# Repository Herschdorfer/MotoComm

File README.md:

# MotoComm
This is the Main Repo for the MotoComm Project

# Thx to Tomas Kovacik for uploading a library to github : https://github.com/tomaskovacik/kicad-library

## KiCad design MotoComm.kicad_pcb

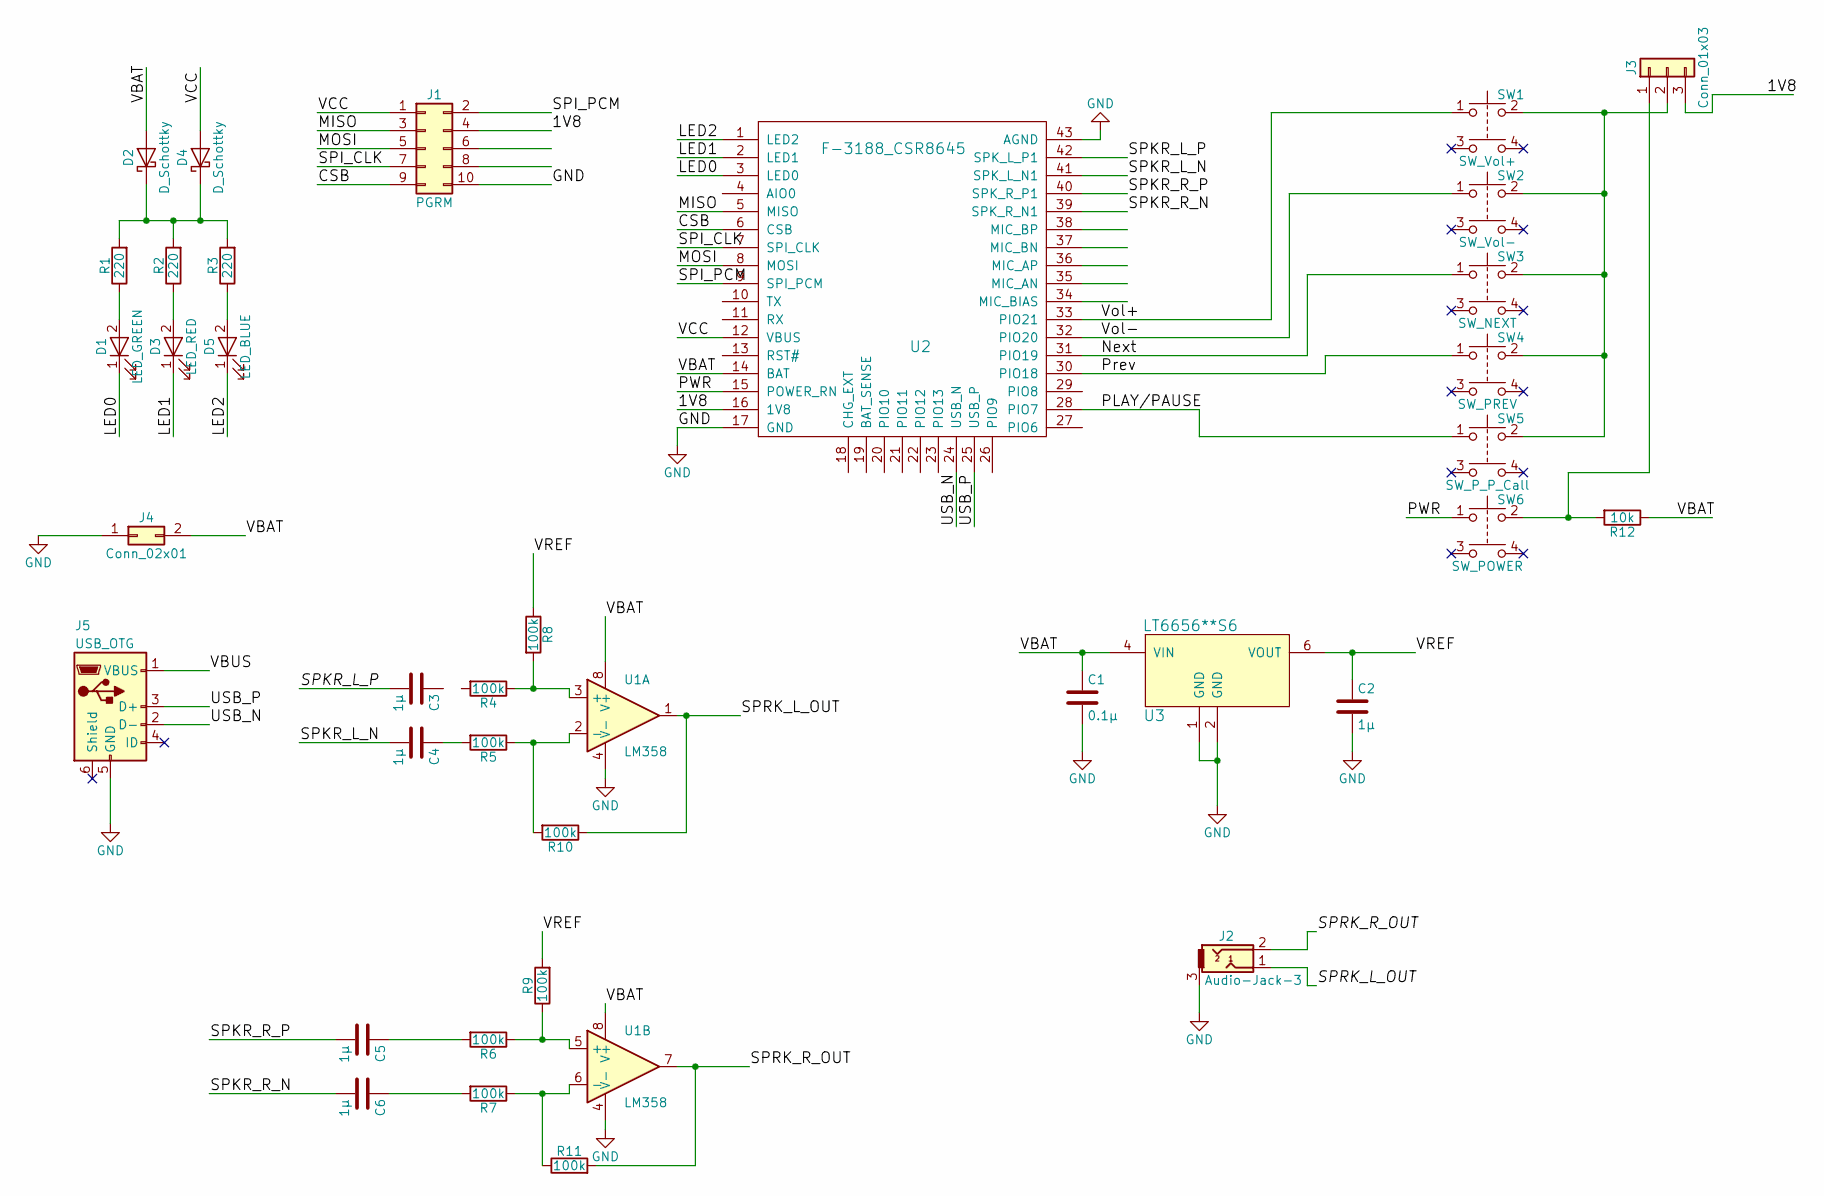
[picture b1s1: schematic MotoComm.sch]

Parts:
C1: 0.1µ; C_0805_HandSoldering
C2, C3, C4, C5, C6: 1µ; C_0805_HandSoldering
D1: LED_GREEN; LED_1206_HandSoldering
D2, D4: D_Schottky; D_1206
D3: LED_RED; LED_1206_HandSoldering
D5: LED_BLUE; LED_1206_HandSoldering
J1: PGRM; Pin_Header_Straight_2x05_Pitch2.54mm
J2: Audio-Jack-3; Stereo_Jack_3.5mm_Switch_Ledino_KB3SPRS
J3: Conn_01x03; Pin_Header_Straight_1x03_Pitch2.54mm
J4: Conn_02x01; JST_ACH_BM02B-ACHSS_02x1.20mm_Angled
J5: USB_OTG; USB_Micro-B
R1, R2, R3: 220; R_0805_HandSoldering
R4, R5, R6, R7, R8, R9, R10, R11: 100k; R_0805_HandSoldering
R12: 10k; R_0805_HandSoldering
SW1: SW_Vol+; SW_TH_Tactile_Omron_B3F-10xx
SW2: SW_Vol-; SW_TH_Tactile_Omron_B3F-10xx
SW3: SW_NEXT; SW_TH_Tactile_Omron_B3F-10xx
SW4: SW_PREV; SW_TH_Tactile_Omron_B3F-10xx
SW5: SW_P_P_Call; SW_TH_Tactile_Omron_B3F-10xx
SW6: SW_POWER; SW_TH_Tactile_Omron_B3F-10xx
U1: LM358; TSSOP-8_3x3mm_Pitch0.65mm
U2: F-3188_CSR8645; F-3188_CSR8645_no_silk_under_antena
U3: LT6656**S6; TSOT-23-8_HandSoldering

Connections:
/1V8: J1.4, J3.3, U2.16 (1V8)
/CSB: J1.9, U2.6 (CSB)
/LED0: D1.1 (K), U2.3 (LED0)
/LED1: D3.1 (K), U2.2 (LED1)
/LED2: D5.1 (K), U2.1 (LED2)
/MISO: J1.3, U2.5 (MISO)
/MOSI: J1.5, U2.8 (MOSI)
/Next: SW3.1, U2.31 (PIO19)
/PLAY/PAUSE: SW5.1, U2.28 (PIO7)
/PWR: SW6.1, U2.15 (POWER_RN)
/Prev: SW4.1, U2.30 (PIO18)
/SPI_CLK: J1.7, U2.7 (SPI_CLK)
/SPI_PCM: J1.2, U2.9 (SPI_PCM)
/SPKR_L_N: C4.2, U2.41 (SPK_L_N1)
/SPKR_L_P: C3.2, U2.42 (SPK_L_P1)
/SPKR_R_N: C6.2, U2.39 (SPK_R_N1)
/SPKR_R_P: C5.2, U2.40 (SPK_R_P1)
/SPRK_L_OUT: J2.1, R10.1, U1.1
/SPRK_R_OUT: J2.2, R11.2, U1.7
/USB_N: J5.2 (D-), U2.24 (USB_N)
/USB_P: J5.3 (D+), U2.25 (USB_P)
/VBAT: C1.1, D2.2 (A), J4.2, R12.1, U1.8 (V+), U2.14 (BAT), U3.4 (VIN)
/VBUS: J5.1 (VBUS)
/VCC: D4.2 (A), J1.1, U2.12 (VBUS)
/VREF: C2.1, R8.1, R9.2, U3.6 (VOUT)
/Vol+: SW1.1, U2.33 (PIO21)
/Vol-: SW2.1, U2.32 (PIO20)
GND: C1.2, C2.2, J1.10, J2.3, J4.1, J5.5 (GND), U1.4 (V-), U2.17 (GND), U2.43 (AGND), U3.1 (GND), U3.2 (GND)
unnamed: C4.1, R5.2
unnamed: C5.1, R6.2
unnamed: C6.1, R7.2
unnamed: D1.2 (A), R1.1
unnamed: D2.1 (K), D4.1 (K), R1.2, R2.2, R3.2
unnamed: D3.2 (A), R2.1
unnamed: D5.2 (A), R3.1
unnamed: J3.1, R12.2, SW6.2
unnamed: J3.2, SW1.2, SW2.2, SW3.2, SW4.2, SW5.2
unnamed: R4.1, R8.2, U1.3 (+)
unnamed: R6.1, R9.1, U1.5 (+)
unnamed: R5.1, R10.2, U1.2 (-)
unnamed: R7.1, R11.1, U1.6 (-)

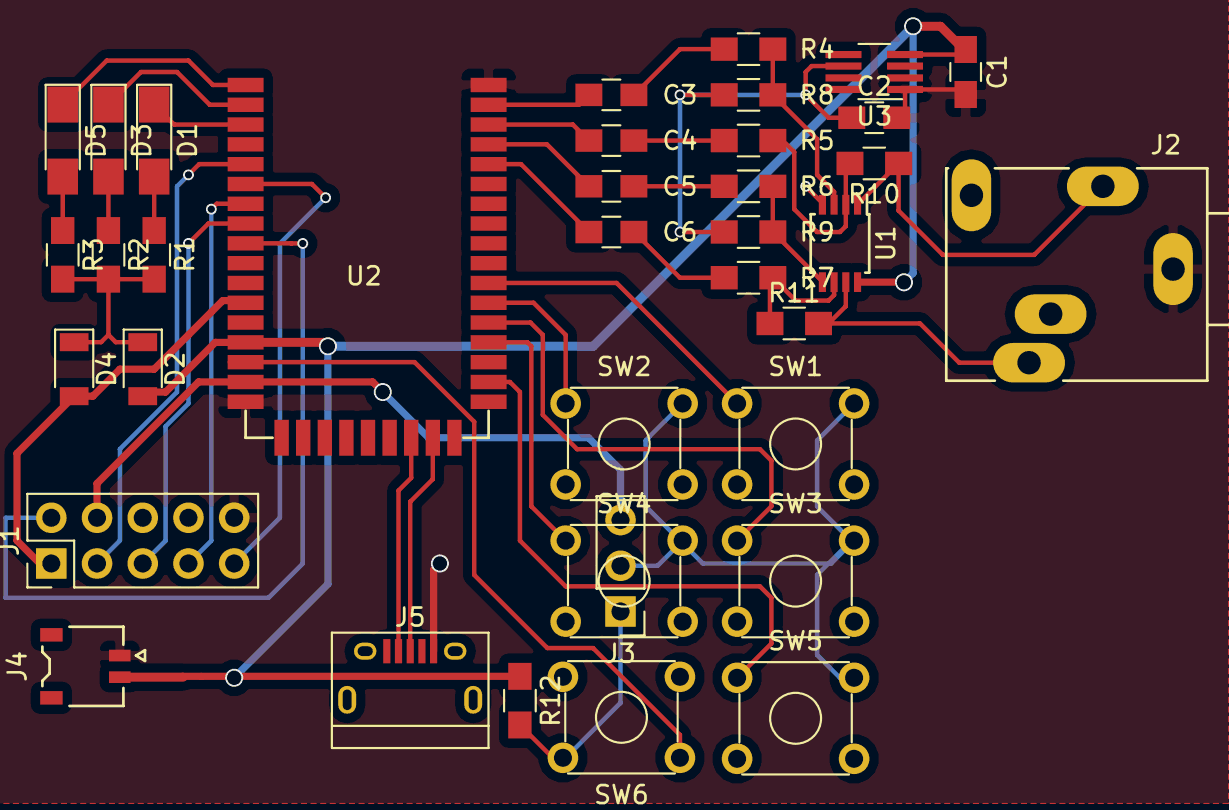
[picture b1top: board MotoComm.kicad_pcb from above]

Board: 2 copper layers, 37 parts (0 on the bottom side), 40 nets.

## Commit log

2018-01-02 inital commit
2018-01-04 first draft with pcb
2018-05-05 minor update
